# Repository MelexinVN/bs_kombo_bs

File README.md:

# БС ("Брейн система")

В рамках проекта ["КомБО"](https://github.com/MelexinVN/bs_kombo) разработана электронная система для проведения интеллектуальных игр.
Система без использования проводной связи позволяет устанавливать точную последовательность нажатий до 20 игровых кнопок.

As part of the project ["КомБО"](https://github.com/MelexinVN/bs_kombo), an electronic system for conducting intellectual games has been developed.
The wireless system allows you to set the exact sequence of pressing up to 20 game buttons.

### Основные характеристики системы

- беспроводная связь базы с игровыми кнопками
- частота радиоканала - 2,4-2,56 ГГц
- дальность связи - 30 м в помещении (может зависеть от зашумленности помещения радиосигналами, перегородок и преград)
- количество кнопок - до 20 шт
- питание каждой игровой кнопки осуществляется от аккумулятора
- питание базы может осуществляться через USB кабель, а также автономно - от аккумулятора

### Main characteristics of the system

- wireless connection of the base with game buttons
- radio channel frequency - 2.4-2.56 GHz
- communication range - 30 m indoors (may depend on the noise level of the room due to radio signals, partitions and obstacles)
- number of buttons - up to 20 pcs.
- each game button is powered by a battery
- the base can be powered via a USB cable, or autonomously - from a battery

### Основные функции системы

- отображение хода игры на дисплее и в специальной программе на ПК
- воспроизведение звуковых файлов (mp3) при различных событиях как через ПК, так и автономно
- возможность замены звуковых файлов
- отдельная индикация первой нажатой игровой кнопки
- возможность перехода очереди нажатых кнопок
- возможность запуска времени и фиксации фальстарта

### Basic system functions

- display of the game progress on the display and in a special program on the PC
- playback of sound files (mp3) for various events both via a PC and autonomously
- ability to replace sound files
- separate indication of the first pressed game button
- the ability to move through the queue of pressed buttons
- ability to start time and fix false start

### Состав системы System composition

Система состоит из базы и комплекта игровых кнопок.

The system consists of a base and a set of game buttons.

База содержит контроллер (stm32f103c8t6 на плате bluepill), дисплей LCD2004, радиомодуль nrf24l01+, кнопки управления, USB-мост CP2102, звуковой модуль DFPlayer mini и схему питания.

The base contains a controller (stm32f103c8t6 on a bluepill board), an LCD2004 display, an nrf24l01+ radio module, control buttons, a CP2102 USB bridge, a DFPlayer mini sound module and a power circuit.

Каждая игровая кнопка содержит схему управления на микроконтроллере stm32f030f4p6 с радиомодулем nrf24l01+, схему питания и аркадную кнопку.

Each game button contains a control circuit on a stm32f030f4p6 microcontroller with an nrf24l01+ radio module, a power circuit and an arcade button.

### Схема соединений игровой кнопки Game Button Connection Diagram

### Программное обеспечение

- МикроПО базы и игровой кнопки написаны в Keil uVision, есть вариант в STM32CubeIDE.
- ПО для ОС Windows написано в Visual Studio.

Все [исходники](https://github.com/MelexinVN/bs_kombo_bs/blob/main/soft) доступны в репозитории.

Готовые файлы прошивок доступны по следующим ссылкам - [прошивка базы](https://disk.yandex.ru/d/3vqxKnFV9-CHBA), [прошивки игровых кнопок (20 штук)](https://disk.yandex.ru/d/9PwJGGSHZjBadQ).

### Software

- The microsoftware base and buttons are written in Keil uVision, there is an option in STM32CubeIDE.
- Software for Windows OS is written in Visual Studio.

All [sources](https://github.com/MelexinVN/bs_kombo_bs/blob/main/soft) are available in the repository.

Ready-made firmware files are available at the following links - [base firmware](https://disk.yandex.ru/d/3vqxKnFV9-CHBA), [gaming button firmware (20 pieces)](https://disk.yandex.ru/d/9PwJGGSHZjBadQ).

### Печатные платы

Печатные платы разработаны в KiCad 7.0, [исходники и гребер файлы](https://github.com/MelexinVN/bs_kombo_bs/blob/main/pcb) также есть в репозитории - [плата контроллера кнопки](https://github.com/MelexinVN/bs_kombo_bs/blob/main/pcb/bs_button_v.1.0), [плата базы](https://github.com/MelexinVN/bs_kombo_bs/blob/main/pcb/bs_base_v.1.0)

### Printed circuit boards

The printed circuit boards were developed in KiCad 7.0, [source and comb files](https://github.com/MelexinVN/bs_kombo_bs/blob/main/pcb) also available in the repository - [button controller board](https://github.com/MelexinVN/bs_kombo_bs/blob/main/pcb/bs_button_v.1.0), [base board](https://github.com/MelexinVN/bs_kombo_bs/blob/main/pcb/bs_base_v.1.0)

### Корпуса

Корпуса и вспомогательные детали изготовлены при помощи 3Д печати.
Модели корпусов разработаны в программе OpenSCAD, [исходники и STL файлы](https://github.com/MelexinVN/bs_kombo_bs/blob/main/3d) доступны в репозитории - [корпус кнопки](https://github.com/MelexinVN/bs_kombo_bs/blob/main/3d/button_box_v.1.0), [корпус и детали базы](https://github.com/MelexinVN/bs_kombo_bs/blob/main/3d/base_box_v.1.0)

### Housings

The housings and auxiliary parts are made using 3D printing.
Case models were developed in the OpenSCAD program, [sources and STL files](https://github.com/MelexinVN/bs_kombo_bs/blob/main/3d) are available in the repository - [button case](https://github.com/MelexinVN/bs_kombo_bs/blob/main/3d/button_box_v.1.0), [body and base details](https://github.com/MelexinVN/bs_kombo_bs/blob/main/3d/base_box_v.1.0)

### Краткое описание работы системы

После включения питания каждой игровой кнопки, ее светодиод производит три коротких моргания (при неисправности радиомодуля - одно). После чего игровая кнопка готова к работе
*Примечание: таким образом можно оценить состояние питания игровой кнопки - при низкой яркости аккумулятор разряжен, при отсутствии морганий возможна неисправность схемы питания*

После включения питания базы на дисплей выводится информация о устройстве, версии ПО, состоянию радиомодуля, номере канала.
Через секунду база отправляет в эфир команду общего сброса. База готова к работе.

На верхней строчке дисплея номера кнопок от "0" до "j"

По нажатию кнопки сброса система возвращается в исходное состояние и также отправляет в эфир команду общего сброса.
**Рекомендуется нажимать кнопку сброса после включения всех кнопок. Если какая то из кнопок была включена после сброса системы, возможна ошибка установления последовательности нажатий!**
Каждая игровая кнопка получившая команду сброса моргает светодиодом один раз.

После того как вся система приведена в готовность, нажатие каждой кнопки будет составлять очередь на второй строке дисплея - также от "0" до "j" и будет вопроизводиться звуковой файл. Светодиод первой нажатой игровой кнопки будет моргать, остальные - светиться.

После нажатия кнопки перехода очереди светодиод первой в очереди игровой кнопки гаснет, моргать начинает следующая в очереди.

Нажатие кнопки пуска времени приводит к началу отсчета времени - воспроизводится соответствующий звуковой сигнал, а на дисплее появляется таймер, отсчитывающий секунды. 

Нажатие кнопки установки приводит к изменению звукового файла, воспроизводимого при нажатии игровой кнопки **ДО** пуска времени. При этом на дисплее появится название звука, один из пяти вариантов.
*Примечание: выбранный звук сохранится после нажатия кнопки сброса, но вернется к стандартному при отключении питания*

Источником звуков при автономной работе является звуковой модуль, аудиовыход которого выведен на корпус в виде аудио гнезда 3,5 мм. Звуковой модуль воспроизводит звуковые файлы формата mp3, записанные на карте памяти microSD. Файлы можно заменить, но они должны иметь те же имена. Стандартное содержимое карты памяти можно найти [тут](https://disk.yandex.ru/d/iv4f7-gtp3TiZA). Файлы должны находиться в корне карты памяти.

**Предусмотрена возможность отображения хода игры и управления системой с помощью программы верхнего уровня. Описание программы и инструкцию можно найти [тут](https://github.com/MelexinVN/bs_kombo_bs/tree/main/soft/Visual%20Studio)**

### Brief description of the system operation

After turning on the power of each game button, its LED produces three short blinks (if the radio module is faulty - one). After which the game button is ready for use
*Note: this way you can evaluate the power status of the game button - if the brightness is low, the battery is discharged, if there is no blinking, the power circuit may be faulty*

After turning on the power of the base, information about the device, software version, radio module status, and channel number is displayed.
A second later, the base sends a general reset command over the air. The base is ready for use.

On the top line of the display there are button numbers from “0” to “j”

When the reset button is pressed, the system returns to its original state and also sends a general reset command over the air.
**It is recommended to press the reset button after all buttons have been turned on. If any of the buttons was turned on after resetting the system, there may be an error in establishing the sequence of presses!**
Each game button that receives a reset command blinks its LED once.

Once the entire system is ready, pressing each button will line up on the second line of the display - also from "0" to "j" - and a sound file will be played. The LED of the first pressed game button will blink, the others will light up.

After pressing the queue switch button, the LED of the first game button in the queue goes out, and the next one in the queue starts blinking.

Pressing the start time button starts the countdown - a corresponding sound signal is played, and a timer appears on the display, counting down the seconds.

Pressing the set button changes the sound file played when the game button **BEFORE** the time starts is pressed. In this case, the name of the sound will appear on the display, one of five options.
*Note: The selected sound will remain after pressing the reset button, but will return to standard when the power is turned off*

The source of sounds during autonomous operation is the sound module, the audio output of which is connected to the case in the form of a 3.5 mm audio jack. The sound module plays mp3 audio files recorded on a microSD memory card. The files can be replaced, but they must have the same names. The standard contents of the memory card can be found [here](https://disk.yandex.ru/d/iv4f7-gtp3TiZA). The files must be located in the root of the memory card.

**It is possible to display the progress of the game and control the system using a top-level program. A description of the program and instructions can be found [here](https://github.com/MelexinVN/bs_kombo_bs/tree/main/soft/Visual%20Studio)**

### Планы по развитию:
- **Переход на более компактную базу с цветным дисплеем**
- **Отображение информации о наличии кнопок в эфире**
- **Отображение информации об уровнях заряда кнопок и базы**
- **Добавление возможности перехода на другие радиоканалы в случае зашумленности помещения**
- **Более гибкая настройка программы верхнего уровня для большей информативности и для разных видов интеллектуальных игр**

### Development plans:
- **Transition to a more compact base with a color display**
- **Displaying information about the presence of buttons on air**
- **Display information about charge levels of buttons and base**
- **Adding the ability to switch to other radio channels in case of a noisy room**
- **More flexible configuration of the top-level program for greater information content and for different types of intellectual games**

## Наши ресурсы:

### Основной репозиторий: [bs_kombo](https://github.com/MelexinVN/bs_kombo)

### Электронная почта: 		    [bskombo@yandex.ru](bskombo@yandex.ru)

### Социальные сети:

- паблик ВКонтакте: 			  [vk.com/bs_kombo](https://vk.com/bs_kombo)
- Telegram-канал: 	        [t.me/bskombo](https://t.me/bskombo)
- Telegram-чат: 	          [t.me/bs_kombo_chat](https://t.me/bs_kombo_chat)

### Авторы всегда рады отзывам и любым конструктивным предложениям по улучшению проекта! 
### The authors are always happy to receive feedback and any constructive suggestions for improving the project!

## Лицензия
Проект распространяется под лицензией Creative Commons Attribution-ShareAlike 4.0 [CC BY-SA 4.0](https://creativecommons.org/licenses/by-sa/4.0/), 
а программное обеспечение - под лицензией GNU General Public License v3.0 [GPL-3.0 license](https://github.com/MelexinVN/bs_kombo/blob/main/LICENSE)

## License
This project is licensed under the Creative Commons 4.0 license with Attribution-ShareAlike [CC BY-SA 4.0](https://creativecommons.org/licenses/by-sa/4.0/), 
and the software is licensed under the GNU General Public License v3.0 [GPL-3.0 license](https://github.com/MelexinVN/bs_kombo/blob/main/LICENSE)

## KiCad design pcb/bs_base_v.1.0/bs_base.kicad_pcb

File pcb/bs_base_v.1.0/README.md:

### Плата базы для "Брейн системы"

- интерактивный перечень элементов - [папка bom](https://github.com/MelexinVN/bs_kombo_bs/blob/main/pcb/bs_base_v.1.0/bom)
- файлы для производства - [папка production](https://github.com/MelexinVN/bs_kombo_bs/blob/main/pcb/bs_base_v.1.0/production/bs_base_2024-06-14_13-07-29)
- гербер-файлы - [bs_button.zip](https://github.com/MelexinVN/bs_kombo_bs/blob/main/pcb/bs_base_v.1.0/production/bs_base_2024-06-14_13-07-29/bs_base.zip) ([облако](https://disk.yandex.ru/d/Mso2Eh_hgUBqgA))

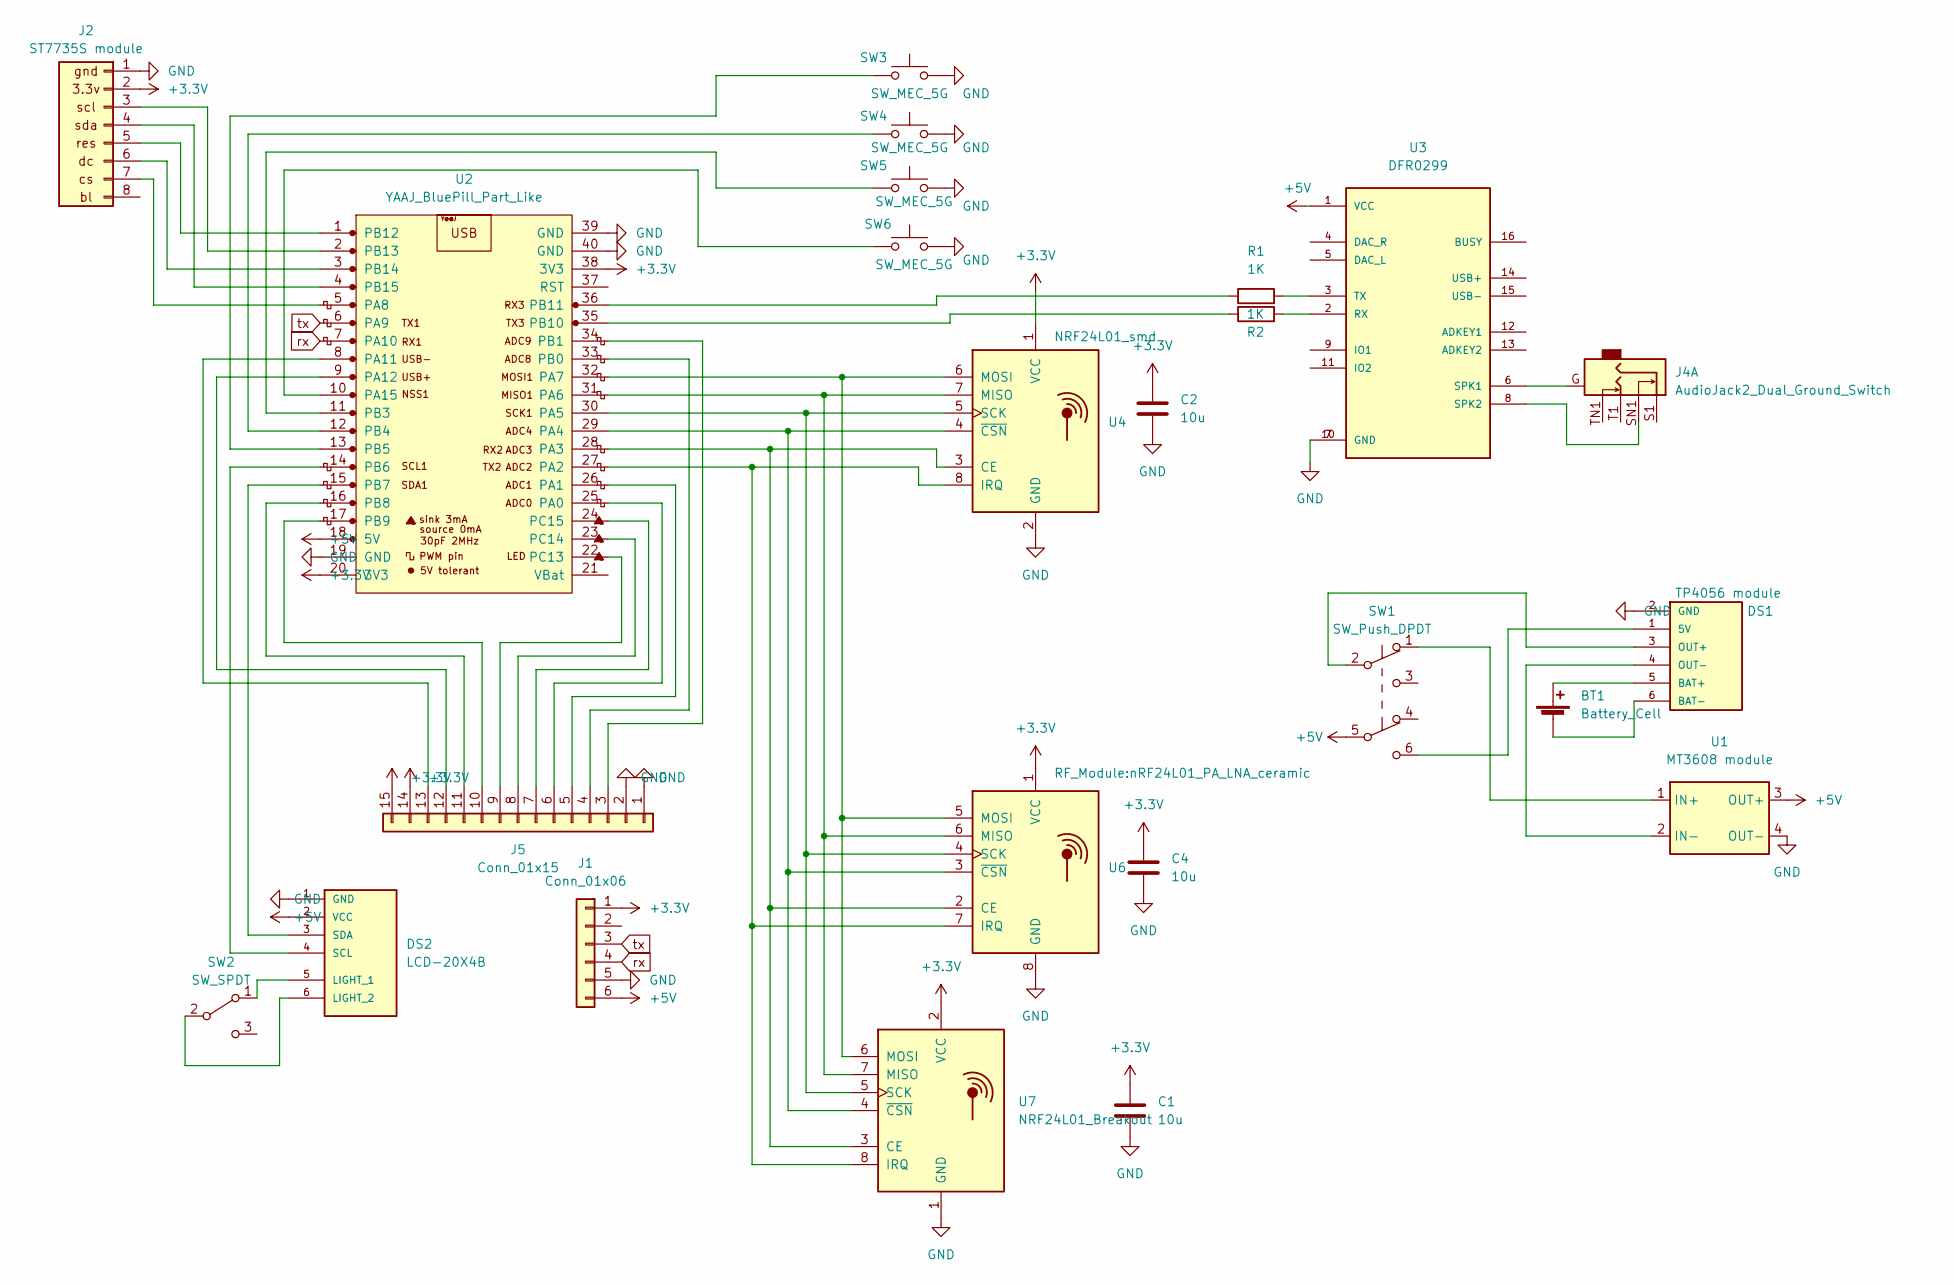
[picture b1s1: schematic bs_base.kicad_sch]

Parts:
BT1: Battery_Cell; PinHeader_1x02_P2.54mm_Vertical
C1, C2, C4: 10u; C_0805_2012Metric_Pad1.18x1.45mm_HandSolder
DS1: TP4056 module; TP4056-18650; PARTREV N/A
DS2: LCD-20X4B; LCD_LCD-20X4B_i2c; PARTREV N/A
J1: Conn_01x06; PinHeader_1x06_P2.54mm_Vertical
J2: ST7735S module; st7735s module
J4: AudioJack2_Dual_Ground_Switch; Jack_3.5mm_CUI_SJ1-3525N_Horizontal
J5: Conn_01x15; PinHeader_1x15_P2.54mm_Vertical
R1, R2: 1K; R_0805_2012Metric_Pad1.20x1.40mm_HandSolder
SW1: SW_Push_DPDT; SW_Push_2P2T_Toggle_CK_PVA2xxH1xxxxxxV2
SW2: SW_SPDT; SW_Slide_1P2T_CK_OS102011MS2Q
SW3, SW4, SW5, SW6: SW_MEC_5G; SW_PUSH_6mm_H13mm
U1: MT3608 module
U2: YAAJ_BluePill_Part_Like; YAAJ_BluePill_1
U3: DFR0299; MODULE_DFR0299
U4: NRF24L01_smd; NRF24L01-Module-SMD
U6: RF_Module:nRF24L01_PA_LNA_ceramic; nRF24L01_PA_LNA_Breakout_smd
U7: NRF24L01_Breakout; nRF24L01_PA_LNA_Breakout

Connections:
+3V3: C1.1, C2.1, C4.1, J1.1, J2.2, J5.14, J5.15, U2.20 (3V3), U2.38 (3V3), U4.1 (VCC), U6.1 (VCC), U7.2 (VCC)
+5V: DS2.2 (VCC), J1.6, SW1.5 (B), U1.3 (OUT+), U2.18 (5V), U3.1 (VCC)
GND: C1.2, C2.2, C4.2, DS1.2 (GND), DS2.1 (GND), J1.5, J2.1, J5.1, J5.2, SW3.1 (A), SW4.1 (A), SW5.1 (A), SW6.1 (A), U1.4 (OUT-), U2.19 (GND), U2.39 (GND), U2.40 (GND), U3.7 (GND), U3.10 (GND), U4.2 (GND), U6.8 (GND), U7.1 (GND)
unnamed: BT1.1 (+), DS1.5 (BAT+)
unnamed: BT1.2 (-), DS1.6 (BAT-)
unnamed: DS1.1 (5V), SW1.6 (C)
unnamed: DS1.3 (OUT+), SW1.2 (B)
unnamed: DS1.4 (OUT-), U1.2 (IN-)
unnamed: DS2.5 (LIGHT_1), SW2.1 (A)
unnamed: DS2.6 (LIGHT_2), SW2.2 (B)
unnamed: DS2.4 (SCL), U2.14 (PB6)
unnamed: DS2.3 (SDA), U2.15 (PB7)
unnamed: J2.3, U2.2 (PB13)
unnamed: J2.4, U2.4 (PB15)
unnamed: J2.5, U2.1 (PB12)
unnamed: J2.6, U2.3 (PB14)
unnamed: J2.7, U2.5 (PA8)
unnamed: J5.3, U2.34 (PB1)
unnamed: J5.4, U2.33 (PB0)
unnamed: J5.5, U2.26 (PA1)
unnamed: J5.6, U2.25 (PA0)
unnamed: J5.7, U2.24 (PC15)
unnamed: J5.8, U2.23 (PC14)
unnamed: J5.9, U2.22 (PC13)
unnamed: J5.10, U2.17 (PB9)
unnamed: J5.11, U2.16 (PB8)
unnamed: J5.12, U2.9 (PA12)
unnamed: J5.13, U2.8 (PA11)
unnamed: SW3.2 (B), U2.13 (PB5)
unnamed: SW4.2 (B), U2.12 (PB4)
unnamed: SW5.2 (B), U2.11 (PB3)
unnamed: SW6.2 (B), U2.10 (PA15)
unnamed: SW1.1 (A), U1.1 (IN+)
unnamed: U2.27 (PA2), U4.8 (IRQ), U6.7 (IRQ), U7.8 (IRQ)
unnamed: U2.28 (PA3), U4.3 (CE), U6.2 (CE), U7.3 (CE)
unnamed: U2.29 (PA4), U4.4 (~CSN), U6.3 (~CSN), U7.4 (~CSN)
unnamed: U2.30 (PA5), U4.5 (SCK), U6.4 (SCK), U7.5 (SCK)
unnamed: U2.31 (PA6), U4.7 (MISO), U6.6 (MISO), U7.7 (MISO)
unnamed: U2.32 (PA7), U4.6 (MOSI), U6.5 (MOSI), U7.6 (MOSI)
unnamed: R2.1, U2.35 (PB10)
unnamed: R1.1, U2.36 (PB11)
unnamed: R2.2, U3.2 (RX)
unnamed: J4.G, U3.6 (SPK1)
unnamed: J4.SN1, U3.8 (SPK2)
unnamed: R1.2, U3.3 (TX)
rx: J1.4, U2.7 (PA10)
tx: J1.3, U2.6 (PA9)

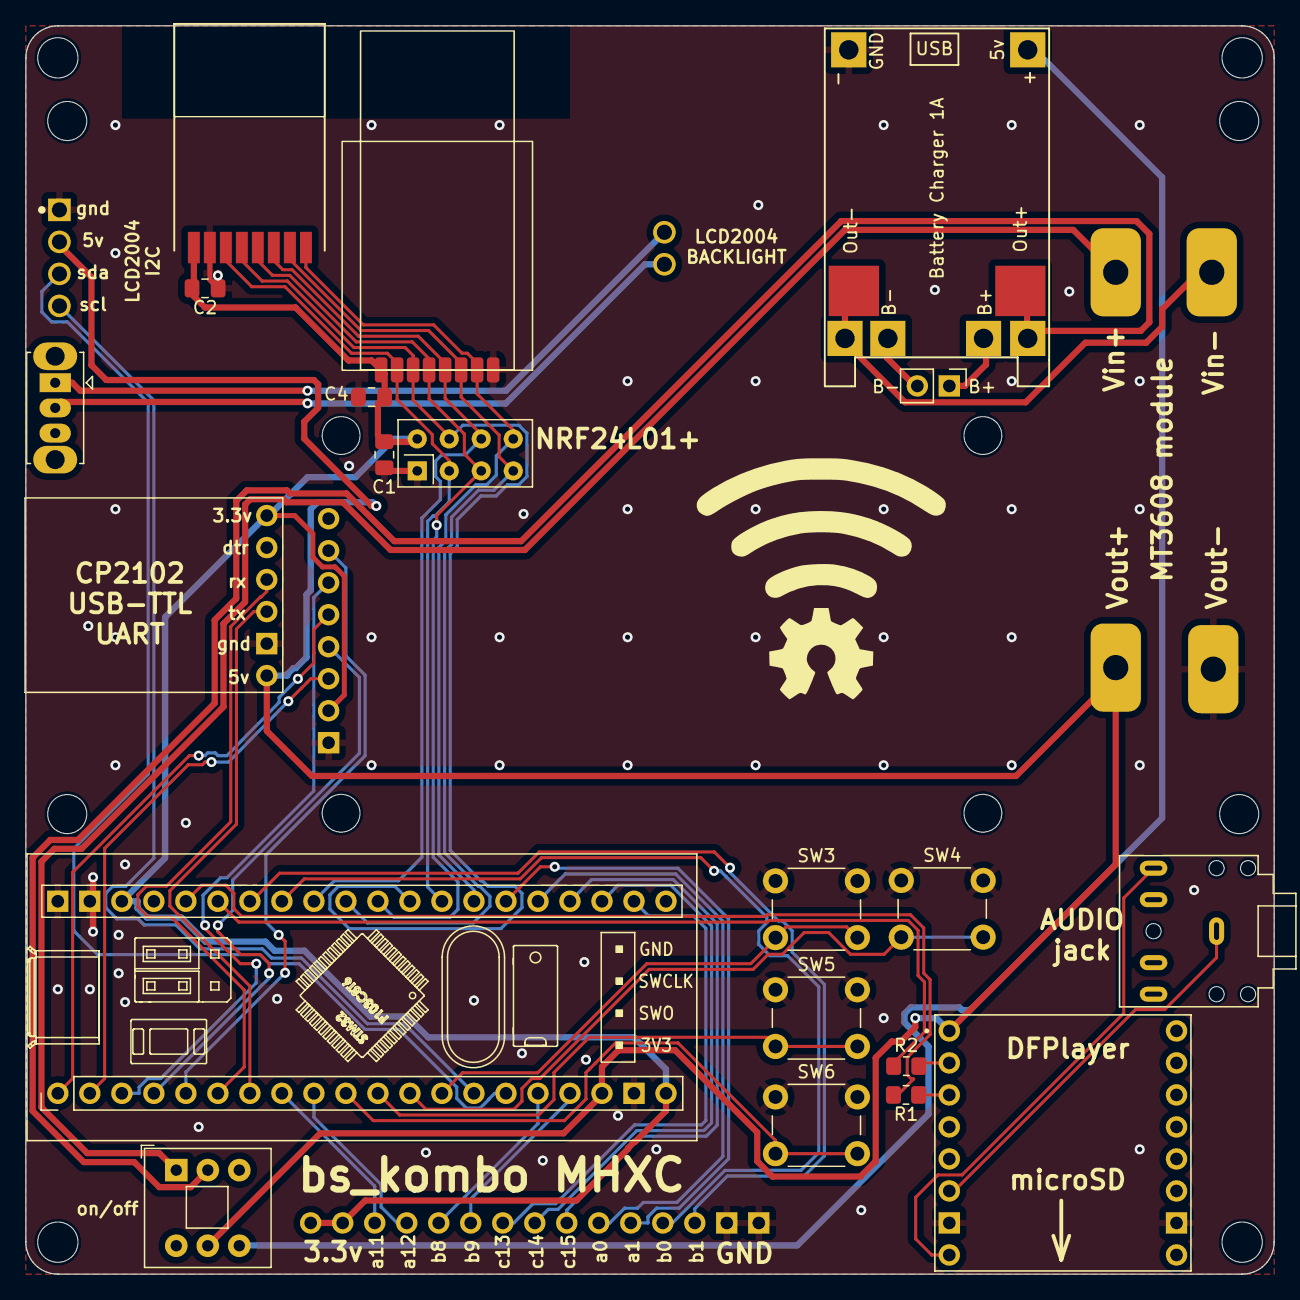
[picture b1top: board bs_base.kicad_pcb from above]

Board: 2 copper layers, 99.1 x 99.1 mm, 24 parts (0 on the bottom side), 47 nets.

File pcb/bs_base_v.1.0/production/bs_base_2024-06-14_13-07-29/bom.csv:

Designator,Footprint,Quantity,Value,LCSC Part #
BT1,PinHeader_1x02_P2.54mm_Vertical,1,Battery_Cell,
"C1, C2, C4",0805,3,10u,
DS1,TP4056-18650,1,TP4056 module,
DS2,LCD_LCD-20X4B_i2c,1,LCD-20X4B,
J1,PinHeader_1x06_P2.54mm_Vertical,1,Conn_01x06,
J2,st7735s module,1,ST7735S module,
J4,Jack_3.5mm_CUI_SJ1-3525N_Horizontal,1,AudioJack2_Dual_Ground_Switch,
J5,PinHeader_1x15_P2.54mm_Vertical,1,Conn_01x15,
"R1, R2",0805,2,1K,
SW1,SW_Push_2P2T_Toggle_CK_PVA2xxH1xxxxxxV2,1,SW_Push_DPDT,
SW2,SW_Slide_1P2T_CK_OS102011MS2Q,1,SW_SPDT,
"SW3, SW4, SW5, SW6",SW_PUSH_6mm_H13mm,4,SW_MEC_5G,
U1,MT3608 module,1,MT3608 module,
U2,YAAJ_BluePill_1,1,YAAJ_BluePill_Part_Like,
U3,MODULE_DFR0299,1,DFR0299,
U4,NRF24L01-Module-SMD,1,NRF24L01_smd,
U6,nRF24L01_PA_LNA_Breakout_smd,1,RF_Module:nRF24L01_PA_LNA_ceramic,
U7,nRF24L01_PA_LNA_Breakout,1,NRF24L01_Breakout,

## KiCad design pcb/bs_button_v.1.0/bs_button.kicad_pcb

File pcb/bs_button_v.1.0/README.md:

### Плата контроллера игровой кнопки для "Брейн системы"

- интерактивный перечень элементов - [папка bom](https://github.com/MelexinVN/bs_kombo_bs/tree/main/pcb/bs_base_v.1.0/bom)
- файлы для производства - [папка production](https://github.com/MelexinVN/bs_kombo_bs/tree/main/pcb/bs_button_v.1.0/production/bs_button_2024-06-14_13-00-54)
- гербер-файлы - [bs_button.zip](https://github.com/MelexinVN/bs_kombo_bs/tree/main/pcb/bs_button_v.1.0/production/bs_button_2024-06-14_13-00-54/bs_button.zip) ([облако](https://disk.yandex.ru/d/F6ybTHqenkIKWQ))

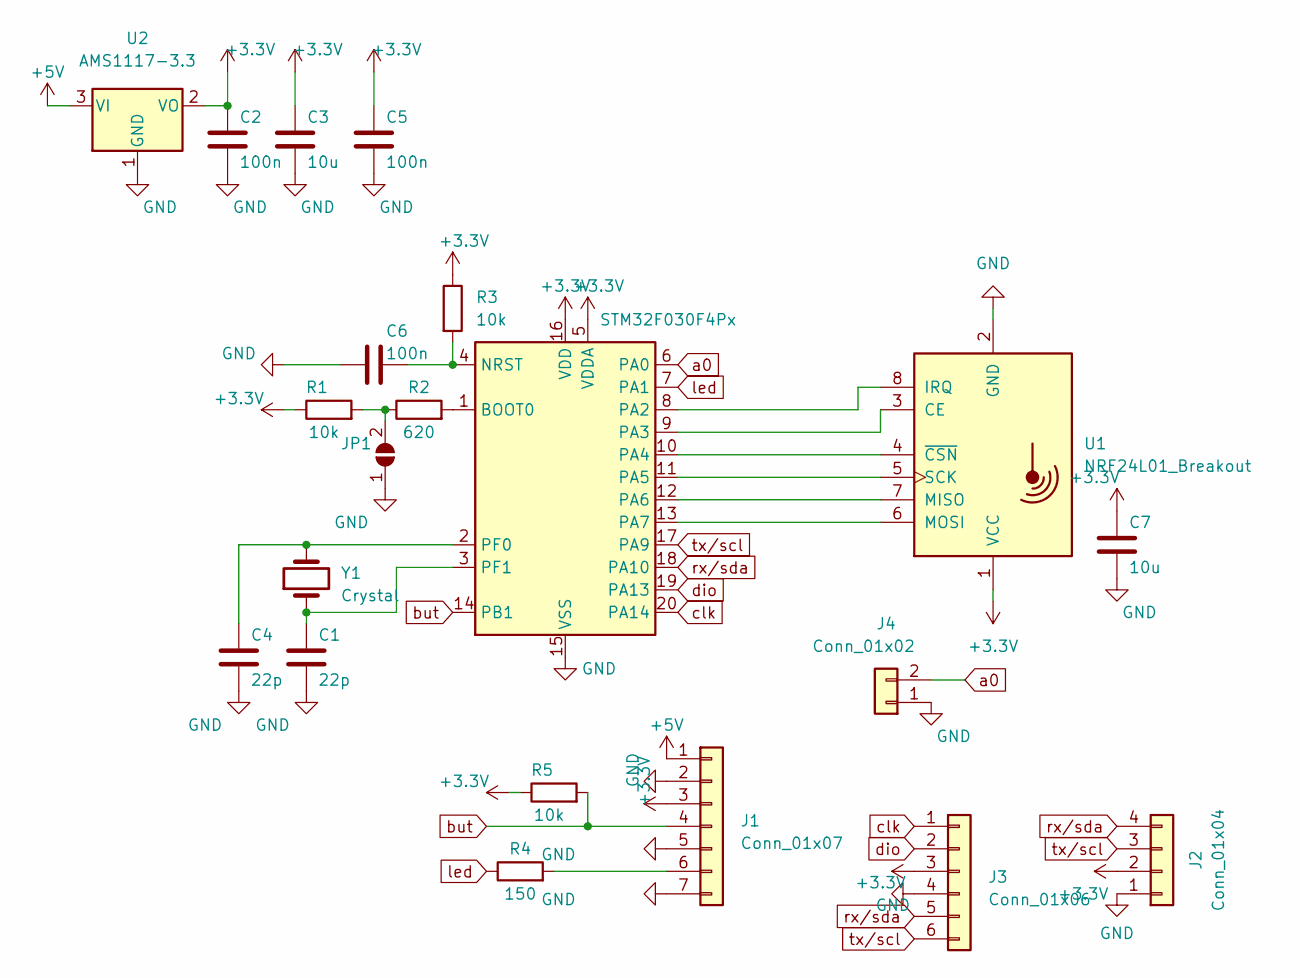
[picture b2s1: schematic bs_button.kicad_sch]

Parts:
C1, C4: 22p; C_0805_2012Metric_Pad1.18x1.45mm_HandSolder
C2, C5, C6: 100n; C_0805_2012Metric_Pad1.18x1.45mm_HandSolder
C3, C7: 10u; C_0805_2012Metric_Pad1.18x1.45mm_HandSolder
J1: Conn_01x07; PinHeader_1x07_P2.54mm_Vertical
J2: Conn_01x04; PinHeader_1x04_P2.54mm_Vertical
J3: Conn_01x06; PinHeader_1x06_P2.54mm_Vertical
J4: Conn_01x02; PinHeader_1x02_P2.54mm_Vertical
JP1: SolderJumper_2_Open; SolderJumper-2_P1.3mm_Open_TrianglePad1.0x1.5mm
R1, R3, R5: 10k; R_0805_2012Metric_Pad1.20x1.40mm_HandSolder
R2: 620; R_0805_2012Metric_Pad1.20x1.40mm_HandSolder
R4: 150; R_0805_2012Metric_Pad1.20x1.40mm_HandSolder
U1: NRF24L01_Breakout; NRF24L01-Module-SMD
U2: AMS1117-3.3; SOT-223-3_TabPin2
U3: STM32F030F4Px; TSSOP-20_4.4x6.5mm_P0.65mm
Y1: Crystal; Crystal_HC49-U_Vertical

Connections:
+3V3: C2.1, C3.1, C5.1, C7.1, J1.3, J2.2, J3.3, R1.1, R3.1, R5.1, U1.1 (VCC), U2.2 (VO), U3.5 (VDDA), U3.16 (VDD)
+5V: J1.1, U2.3 (VI)
GND: C1.2, C2.2, C3.2, C4.2, C5.2, C6.2, C7.2, J1.2, J1.5, J1.7, J2.1, J3.4, J4.1, JP1.1 (A), U1.2 (GND), U2.1 (GND), U3.15 (VSS)
unnamed: J1.6, R4.2
unnamed: JP1.2 (B), R1.2, R2.1
unnamed: U1.3 (CE), U3.9 (PA3)
unnamed: U1.8 (IRQ), U3.8 (PA2)
unnamed: U1.7 (MISO), U3.12 (PA6)
unnamed: U1.6 (MOSI), U3.13 (PA7)
unnamed: U1.5 (SCK), U3.11 (PA5)
unnamed: U1.4 (~CSN), U3.10 (PA4)
unnamed: R2.2, U3.1 (BOOT0)
unnamed: C6.1, R3.2, U3.4 (NRST)
unnamed: C4.1, U3.2 (PF0), Y1.2
unnamed: C1.1, U3.3 (PF1), Y1.1
a0: J4.2, U3.6 (PA0)
but: J1.4, R5.2, U3.14 (PB1)
clk: J3.1, U3.20 (PA14)
dio: J3.2, U3.19 (PA13)
led: R4.1, U3.7 (PA1)
rx/sda: J2.4, J3.5, U3.18 (PA10)
tx/scl: J2.3, J3.6, U3.17 (PA9)

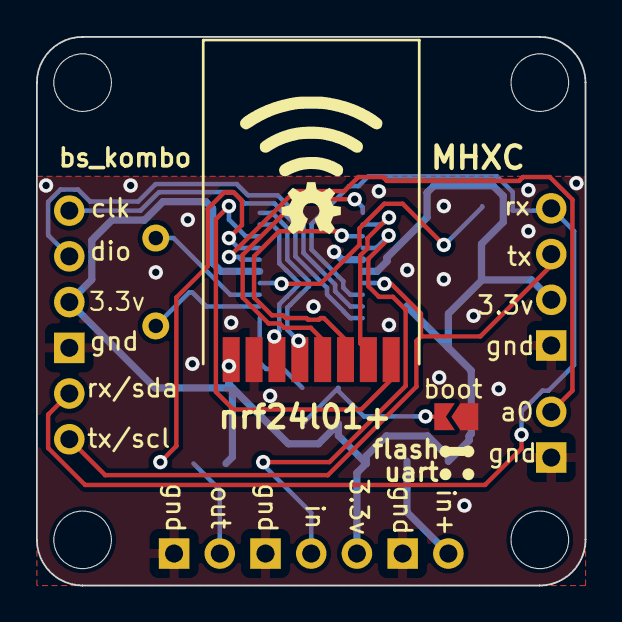
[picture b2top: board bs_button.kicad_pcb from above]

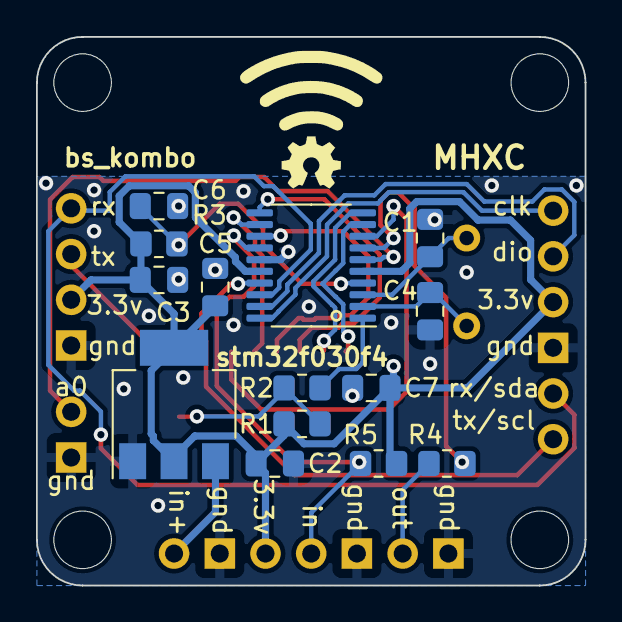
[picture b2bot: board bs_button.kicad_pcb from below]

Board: 2 copper layers, 30.5 x 30.5 mm, 21 parts (14 on the bottom side), 22 nets.

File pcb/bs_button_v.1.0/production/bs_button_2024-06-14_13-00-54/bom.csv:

Designator,Footprint,Quantity,Value,LCSC Part #
"C1, C4",0805,2,22p,
"C2, C5, C6",0805,3,100n,
"C3, C7",0805,2,10u,
J1,PinHeader_1x07_P2.54mm_Vertical,1,Conn_01x07,
J2,PinHeader_1x04_P2.54mm_Vertical,1,Conn_01x04,
J3,PinHeader_1x06_P2.54mm_Vertical,1,Conn_01x06,
J4,PinHeader_1x02_P2.54mm_Vertical,1,Conn_01x02,
JP1,SolderJumper-2_P1.3mm_Open_TrianglePad1.0x1.5mm,1,SolderJumper_2_Open,
"R1, R3, R5",0805,3,10k,
R2,0805,1,620,
R4,0805,1,150,
U1,NRF24L01-Module-SMD,1,NRF24L01_Breakout,
U2,SOT-223-3_TabPin2,1,AMS1117-3.3,
U3,TSSOP-20_4.4x6.5mm_P0.65mm,1,STM32F030F4Px,
Y1,Crystal_HC49-U_Vertical,1,Crystal,

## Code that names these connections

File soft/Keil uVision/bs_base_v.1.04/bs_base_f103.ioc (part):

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Mcu.Name=STM32F103C(8-B)Tx
Mcu.Package=LQFP48
Mcu.UserName=STM32F103C8Tx
PA10.Mode=Asynchronous
PA10.Signal=USART1_RX
PA13.Mode=Serial_Wire
PA13.Signal=SYS_JTMS-SWDIO
PA14.Mode=Serial_Wire
PA14.Signal=SYS_JTCK-SWCLK
PA15.GPIOParameters=GPIO_PuPd,GPIO_Label,GPIO_ModeDefaultEXTI
PA15.GPIO_Label=TIME
PA15.GPIO_ModeDefaultEXTI=GPIO_MODE_IT_FALLING
PA15.GPIO_PuPd=GPIO_PULLUP
PA15.Signal=GPXTI15
PA2.GPIOParameters=GPIO_Label,GPIO_ModeDefaultEXTI
PA2.GPIO_Label=IRQ
PA2.GPIO_ModeDefaultEXTI=GPIO_MODE_IT_FALLING
PA2.Signal=GPXTI2
PA3.GPIOParameters=GPIO_Label
PA3.GPIO_Label=CE
PA3.Signal=GPIO_Output
PA4.GPIOParameters=GPIO_Label
PA4.GPIO_Label=CSN
PA4.Signal=GPIO_Output
PA5.Mode=Full_Duplex_Master
PA5.Signal=SPI1_SCK
PA6.Mode=Full_Duplex_Master
PA6.Signal=SPI1_MISO
PA7.Mode=Full_Duplex_Master
PA7.Signal=SPI1_MOSI
PA8.Signal=GPIO_Output
PA9.Mode=Asynchronous
PA9.Signal=USART1_TX
PB10.Mode=Asynchronous
PB10.Signal=USART3_TX
PB11.Mode=Asynchronous
PB11.Signal=USART3_RX
PB12.Signal=GPIO_Output
PB13.Mode=Simplex_Bidirectional_Master
PB13.Signal=SPI2_SCK
PB14.Signal=GPIO_Output
PB15.Mode=Simplex_Bidirectional_Master
PB15.Signal=SPI2_MOSI
PB3.GPIOParameters=GPIO_PuPd,GPIO_Label,GPIO_ModeDefaultEXTI
PB3.GPIO_Label=NEXT
PB3.GPIO_ModeDefaultEXTI=GPIO_MODE_IT_FALLING
PB3.GPIO_PuPd=GPIO_PULLUP
PB3.Signal=GPXTI3
PB4.GPIOParameters=GPIO_PuPd,GPIO_Label,GPIO_ModeDefaultEXTI
PB4.GPIO_Label=RST
PB4.GPIO_ModeDefaultEXTI=GPIO_MODE_IT_FALLING
PB4.GPIO_PuPd=GPIO_PULLUP
PB4.Signal=GPXTI4
PB5.GPIOParameters=GPIO_PuPd,GPIO_Label,GPIO_ModeDefaultEXTI
PB5.GPIO_Label=SET
PB5.GPIO_ModeDefaultEXTI=GPIO_MODE_IT_FALLING
PB5.GPIO_PuPd=GPIO_PULLUP
PB5.Signal=GPXTI5
PB6.Mode=I2C
PB6.Signal=I2C1_SCL
PB7.Mode=I2C
PB7.Signal=I2C1_SDA
PC13-TAMPER-RTC.GPIOParameters=GPIO_Label
PC13-TAMPER-RTC.GPIO_Label=LED
PC13-TAMPER-RTC.Signal=GPIO_Output
PD0-OSC_IN.Mode=HSE-External-Oscillator
PD0-OSC_IN.Signal=RCC_OSC_IN
PD1-OSC_OUT.Mode=HSE-External-Oscillator
PD1-OSC_OUT.Signal=RCC_OSC_OUT
RCC.SYSCLKFreq_VALUE=72000000
RCC.SYSCLKSource=RCC_SYSCLKSOURCE_PLLCLK
board=custom

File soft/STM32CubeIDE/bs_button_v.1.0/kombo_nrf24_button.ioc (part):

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Mcu.Name=STM32F030F4Px
Mcu.Package=TSSOP20
Mcu.UserName=STM32F030F4Px
PA1.GPIOParameters=GPIO_Label
PA1.GPIO_Label=LED
PA1.Signal=GPIO_Output
PA13.Mode=Serial_Wire
PA13.Signal=SYS_SWDIO
PA14.Mode=Serial_Wire
PA14.Signal=SYS_SWCLK
PA2.GPIOParameters=GPIO_Label,GPIO_ModeDefaultEXTI
PA2.GPIO_Label=IRQ
PA2.GPIO_ModeDefaultEXTI=GPIO_MODE_IT_FALLING
PA2.Signal=GPXTI2
PA3.GPIOParameters=GPIO_Label
PA3.GPIO_Label=CE
PA3.Signal=GPIO_Output
PA4.GPIOParameters=GPIO_Label
PA4.GPIO_Label=CSN
PA4.Signal=GPIO_Output
PA5.Mode=Full_Duplex_Master
PA5.Signal=SPI1_SCK
PA6.Mode=Full_Duplex_Master
PA6.Signal=SPI1_MISO
PA7.Mode=Full_Duplex_Master
PA7.Signal=SPI1_MOSI
PB1.GPIOParameters=GPIO_PuPd,GPIO_Label,GPIO_ModeDefaultEXTI
PB1.GPIO_Label=BUT
PB1.GPIO_ModeDefaultEXTI=GPIO_MODE_IT_FALLING
PB1.GPIO_PuPd=GPIO_PULLUP
PB1.Signal=GPXTI1
PF0-OSC_IN.Mode=HSE-External-Oscillator
PF0-OSC_IN.Signal=RCC_OSC_IN
PF1-OSC_OUT.Mode=HSE-External-Oscillator
PF1-OSC_OUT.Signal=RCC_OSC_OUT
RCC.SYSCLKFreq_VALUE=48000000
RCC.SYSCLKSource=RCC_SYSCLKSOURCE_PLLCLK
board=custom

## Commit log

2024-06-24 update media
2024-08-23 first update
    Проект прошивки базы заменен на более актуальный.
    Добавлены новые варианты корпуса игровых кнопок
2024-10-23 Корректировка схемы
